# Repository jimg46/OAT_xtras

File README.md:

# OAT_xtras
OpenAstroTracker bits and pieces

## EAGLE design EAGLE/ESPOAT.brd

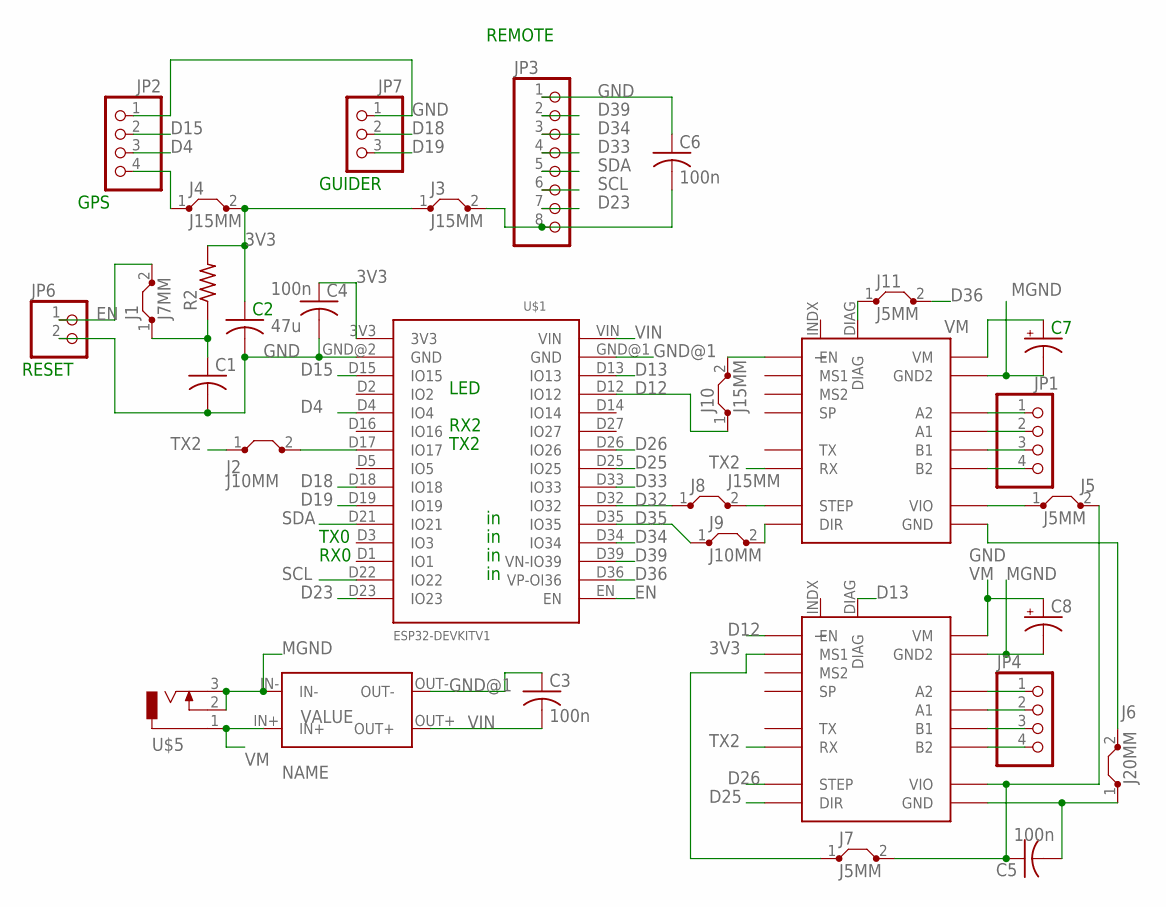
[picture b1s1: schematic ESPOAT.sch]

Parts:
C1: C-US025-030X050; C025-030X050
C2: 47u; C050-024X044
C3, C4, C5, C6: 100n; C050-024X044
C7, C8: CPOL-USE5-8.5; E5-8,5
J1: J7MM; 07
J2, J9: J10MM; 10
J3, J4, J8, J10: J15MM; 15
J5, J7, J11: J5MM; 05
J6: J20MM; 20
JP1, JP2, JP4: PINHD-1X4; 1X04
JP3: PINHD-1X8; 1X08
JP6: PINHD-1X2; 1X02
JP7: PINHD-1X3; 1X03
R2: R-US_0207/10; 0207/10
U$1: ESP32DEVKITV1; ESP32-DEVKITV1
U$2, U$3: FY2209V3
U$4: MINI-360
U$5: PS0520; DCJ0203

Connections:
3V3: C2.1, C4.1, J3.1, J4.2, J7.1, R2.2, U$1.3V3, U$3.MS1
D4: JP2.3, U$1.D4 (IO4)
D12: J10.1, U$1.D12 (IO12), U$3.EN
D13: U$1.D13 (IO13), U$3.DIAG
D15: JP2.2, U$1.D15 (IO15)
D18: JP7.2, U$1.D18 (IO18)
D19: JP7.3, U$1.D19 (IO19)
D23: JP3.7, U$1.D23 (IO23)
D25: U$1.D25 (IO25), U$3.DIR
D26: U$1.D26 (IO26), U$3.STP (STEP)
D32: J8.1, U$1.D32 (IO32)
D33: JP3.4, U$1.D33 (IO33)
D34: JP3.3, U$1.D34 (IO34)
D35: J9.1, U$1.D35 (IO35)
D36: J11.2, U$1.D36 (VP-OI36)
D39: JP3.2, U$1.D39 (VN-IO39)
EN: J1.2, JP6.1, U$1.EN
GND: C1.2, C2.2, C4.2, C6.1, J6.2, JP2.1, JP3.1, JP6.2, JP7.1, U$1.GND@2 (GND), U$2.GND
GND@1: C3.1, U$1.GND@1 (GND), U$4.OUT-
MGND: C7.-, C8.-, U$2.GND2, U$3.GND2, U$4.IN-, U$5.2, U$5.3
unnamed: JP1.4, U$2.B2
unnamed: J8.2, U$2.STP (STEP)
unnamed: C1.1, J1.1, R2.1
unnamed: J2.2, U$1.D17 (IO17)
unnamed: JP1.3, U$2.B1
unnamed: C5.1, J5.2, J7.2, U$3.VIO
unnamed: J4.1, JP2.4
unnamed: J5.1, U$2.VIO
unnamed: C5.2, J6.1, U$3.GND
unnamed: J9.2, U$2.DIR
unnamed: J10.2, U$2.EN
unnamed: JP1.2, U$2.A1
unnamed: JP1.1, U$2.A2
unnamed: JP4.1, U$3.A2
unnamed: JP4.2, U$3.A1
unnamed: JP4.3, U$3.B1
unnamed: JP4.4, U$3.B2
unnamed: J11.1, U$2.DIAG
unnamed: C6.2, J3.2, JP3.8
SCL: JP3.6, U$1.D22 (IO22)
SDA: JP3.5, U$1.D21 (IO21)
TX2: J2.1, U$2.RX, U$3.RX
VIN: C3.2, U$1.VIN, U$4.OUT+
VM: C7.+, C8.+, U$2.VM, U$3.VM, U$4.IN+, U$5.1

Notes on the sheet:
LED
TX0
RX0
REMOTE
GPS
RESET
GUIDER
TX2
RX2

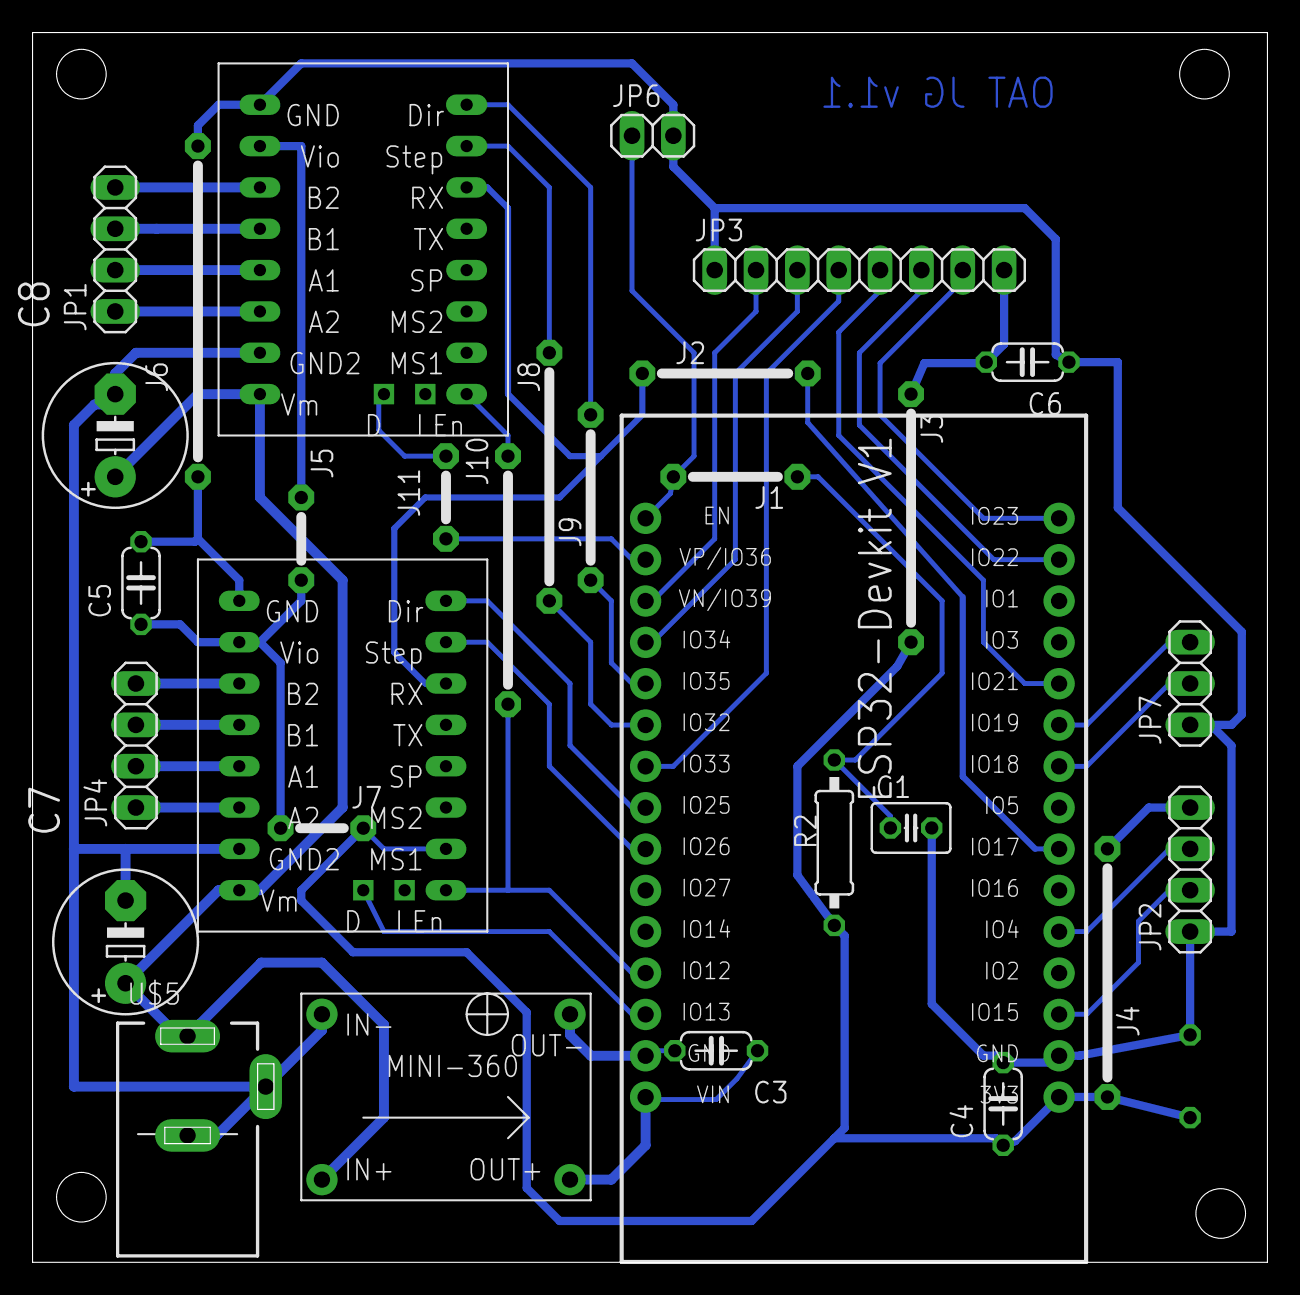
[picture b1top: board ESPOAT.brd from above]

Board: 2 copper layers, 75.9 x 75.6 mm, 31 parts (1 on the bottom side), 44 nets.
